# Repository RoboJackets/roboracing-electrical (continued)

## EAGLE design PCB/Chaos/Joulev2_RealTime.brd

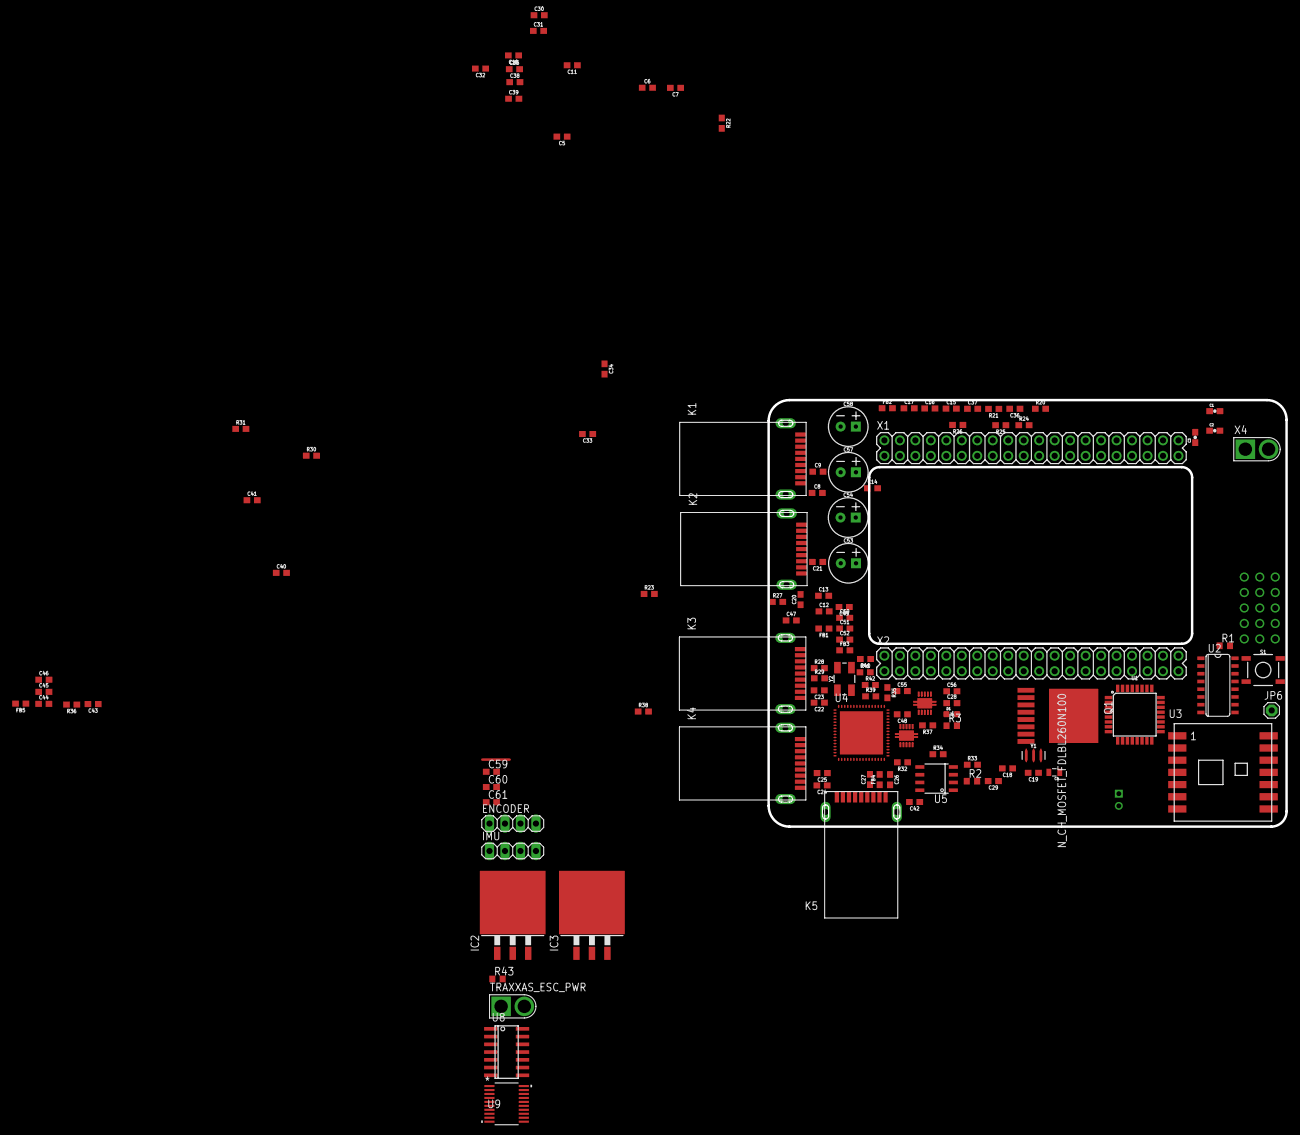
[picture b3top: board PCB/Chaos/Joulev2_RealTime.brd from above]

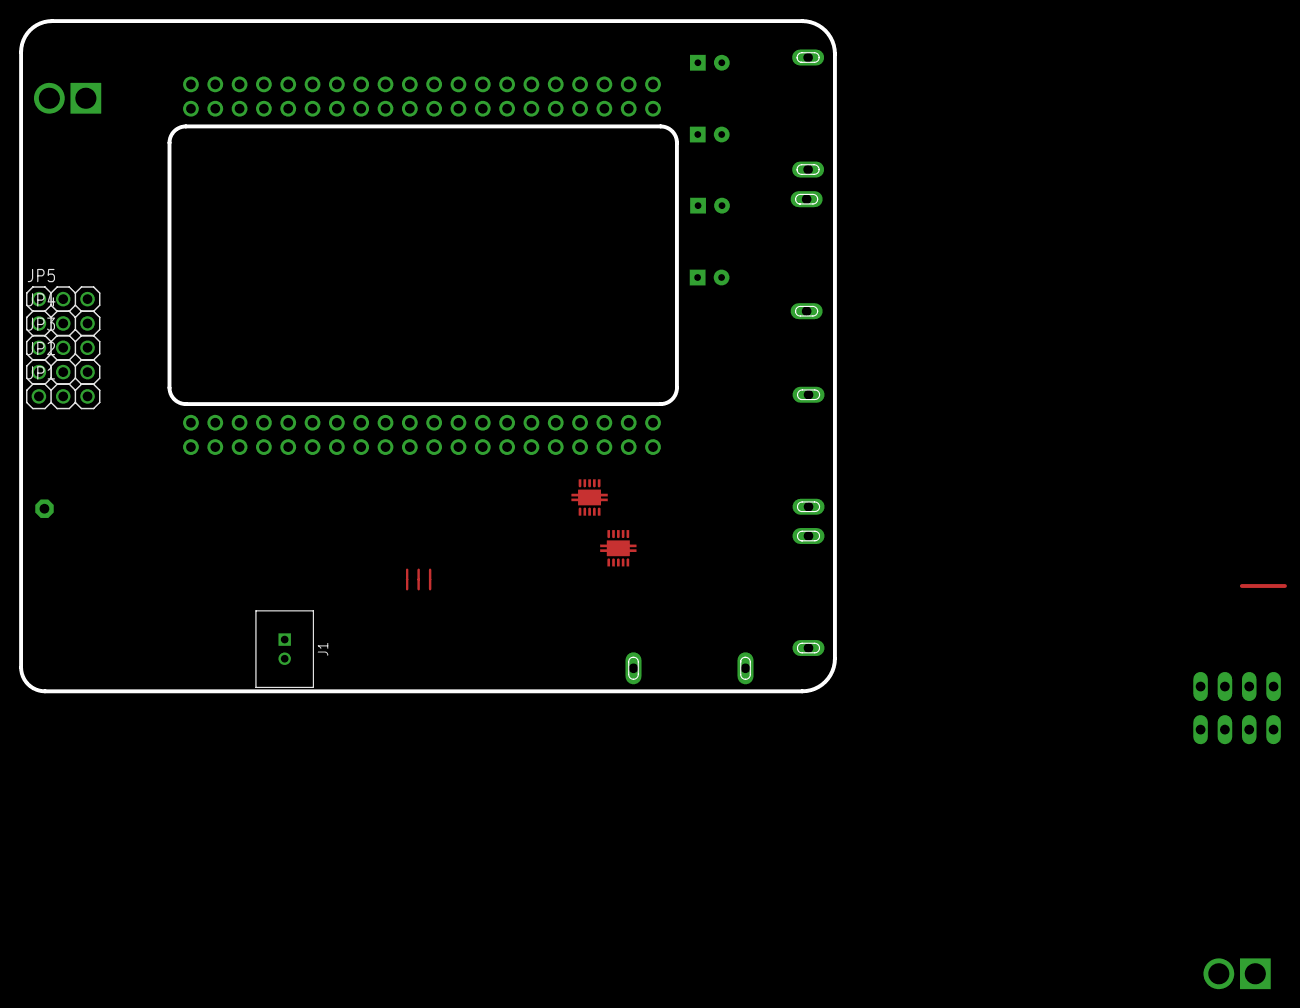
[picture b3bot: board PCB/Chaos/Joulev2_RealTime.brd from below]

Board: 2 copper layers, 85.0 x 70.0 mm, 127 parts (6 on the bottom side), 98 nets.

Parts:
C1: 0.22uF; 0603-CAP
C2: .1uF; 0603-CAP
C3: 0.1uF; 0603-CAP
C4: 10uf; 0805@1
C5, C10, C16, C19, C33: 1nF; 0603
C6, C8, C9, C12, C13, C17, C18, C20, C21, C22, C23, C24, C25, C26, C27, C28, C29, C31, C32, C35, C36, C37, C38, C39, C40, C41, C44, C45, C46, C47, C48, C49, C51, C52, C55, C56: 0.1uF; 0603
C7, C30, C50: 10uF; 0603
C11: 1.0uF; 0603
C14, C15: 18pF; 0603
C34, C43: 4.7uF; 0603
C42: 10nF; 0603
C53, C54, C57, C58: 150uF; CPOL-RADIAL-2.5MM-6.5MM
C59, C60: 0.1uF; C0603
C61: 10uF; C0603
D1: LED-0603
ENCODER: 1X04
FB1, FB2, FB3, FB5: 220@100MHz; 0603
FB4: 220@100Mhz; 0603
IC2, IC3: LM340S-12; TO263-3
IMU: 1X04
J1: 2-PIN_2MM-V; 2MM-2-V
JP1, JP2, JP3, JP4, JP5: 1X03
JP6: antenna; 1X01
K1, K2, K3, K4, K5: 692112030100
Q1: N_CH_MOSFET_FDLBL260N100; MO-299A
R1, R2, R43: 10k ohm; R0603
R3: 680 ohm; R0603
R20, R21, R26, R30, R31, R36: 1M; 0603
R22: 90.9k; 0603
R23, R39, R40, R41, R42: 10k; 0603
R24, R25, R27, R29, R32, R33, R34, R35: 4.7k; 0603
R28: 9.53k; 0603
R37, R38: 25.5k; 0603
S1: MOMENTARY-SWITCH 5.2mm; TACTILE_SWITCH_SMD_5.2MM
TRAXXAS_ESC_PWR: TRAXXAS-CON
U1: ATMEGA328P_TQFP; TQFP32-08
U2: 74VHC_MUXSO16; SO16
U3: RFM69CW; RFM69CW-XXXS2
U4: TUSB8041; QFN64-9X9
U5: ADP1706ARDZ-1.1-R7; SOIC8
U6, U7: TPS2561DRCT; 10-VSON
U8: SOIC-14
U9: TXB0108PWR; PW20
X1: J12HEADER_(JOULE); 2X20
X2: J13HEADER_(JOULE); 2X20
X4: TRAXXAS-CON
Y1: 16MHz; RESONATOR-SMD-3.2X1.3
Y2: 24MHz; CRYSTAL-SMD-5X3.2-4PAD

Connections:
1.1V: C30.1, C31.1, C32.1, C35.1, C38.1, C39.1, C40.1, C41.1, C43.1, U4.5, U4.8, U4.13, U4.21, U4.28, U4.31, U4.51, U4.57, U5.5, U5.6, U5.7
3.3V: C3.1, C4.1, C34.1, FB5.2, R32.2, R33.2, R34.2, R35.2, R39.2, R40.2, R41.2, R42.2, U3.2, U5.1, U5.3, U5.4
5V: C2.1, R1.1, R3.2, U1.4, U1.6, U1.18, U2.16
5V_MODE_SELECT: U1.12, U2.1
+3V3_HUB: C44.1, C45.1, C46.1, C47.1, C50.1, FB5.1
+5V: C48.1, C49.1, U6.2_1, U6.2_2, U6.3_1, U6.3_2, U7.2_1, U7.2_2, U7.3_1, U7.3_2
DN1_VBUS: C51.1, C53.1, FB1.1, U6.9_1, U6.9_2
DN2_VBUS: C55.1, C57.1, FB2.1, U6.8_1, U6.8_2
DN3_VBUS: C52.1, C54.1, FB3.1, U7.9_1, U7.9_2
ESTOP: J1.1, U1.2
ESTOP_GATE: J1.2, Q1.GATE, R2.1
GND: C1.2, C2.2, C3.2, C4.2, C5.1, C5.2, C6.1, C6.2, C7.2, C10.1, C10.2, C11.2, C12.2, C13.1, C13.2, C14.1, C15.1, C16.1, C16.2, C17.2, C18.1, C18.2, C19.1, C19.2, C28.2, C29.1, C29.2, C30.2, C31.2, C32.2, C33.1, C33.2, C34.2, C35.2, C36.2, C37.1, C37.2, C38.2, C39.2, C40.2, C41.2, C42.2, C43.2, C44.2, C45.2, C46.2, C47.2, C48.2, C49.2, C50.2, C51.2, C52.2, C53.2, C54.2, C55.2, C56.2, C57.2, C58.2, D1.C, JP1.1, JP2.1, JP3.1, JP4.1, K1.4, K1.7, K2.4, K2.7, K3.4, K3.7, K4.4, K5.4, Q1.P2, Q1.P3, Q1.P4, Q1.P5, Q1.P6, Q1.P7, Q1.P8, R2.2, R20.1, R20.2, R21.1, R21.2, R23.1, R24.1, R25.1, R27.1, R28.1, R29.1, R30.1, R30.2, R31.1, R31.2, R36.1, R36.2, R37.1, R38.1, S1.3, U1.3, U1.5, U1.21, U2.8, U3.3, U3.14, U4.16, U4.34, U4.52, U4.63, U4.EXP, U5.2, U6.1_1, U6.1_2, U6.PAD1, U6.PAD2, U6.PAD3, U7.1_1, U7.1_2, U7.PAD1, U7.PAD2, U7.PAD3, X1.36, X1.37, X1.38, X1.39, X2.1, X2.3, X2.5, X2.7, X2.9, X4.GND, Y1.2
GRST#: C11.1, U4.50
ILIM1: R37.2, U6.7_1, U6.7_2
ILIM2: R38.2, U7.7_1, U7.7_2
MISO_3P3V: U3.8, X2.29
MOSI_3P3V: U3.5, X2.27
unnamed: JP6.1, U3.1
unnamed: JP4.3, U2.4
unnamed: JP5.3, U2.7
unnamed: R1.2, S1.1, U1.29
unnamed: U1.7, Y1.1
unnamed: JP1.2, JP2.2, JP3.2, JP4.2, JP5.2
unnamed: U1.8, Y1.3
unnamed: R28.2, U4.64
unnamed: JP2.3, U2.3
unnamed: JP3.3, U2.6
unnamed: R29.2, U4.49
unnamed: D1.A, R3.1
unnamed: R27.2, U4.45
unnamed: R25.2, U4.42
unnamed: R24.2, U4.40
unnamed: R22.2, R23.2, U4.48
unnamed: C27.1, U4.27
unnamed: C26.1, U4.26
unnamed: C25.1, U4.20
unnamed: C24.1, U4.19
unnamed: C23.1, U4.12
unnamed: C22.1, U4.11
unnamed: C21.1, U4.4
unnamed: C20.1, U4.3
unnamed: C12.1, FB1.2, K2.1
unnamed: C42.1, U5.8
unnamed: C17.1, FB2.2
unnamed: C28.1, FB3.2, K4.1
unnamed: C56.1, C58.1, U7.8_1, U7.8_2
unnamed: C36.1, FB4.2, K5.1
OVERCUR1Z: R39.1, U4.46, U6.10_1, U6.10_2
OVERCUR2Z: R41.1, U4.47, U6.6_1, U6.6_2
OVERCUR3Z: R40.1, U4.44, U7.10_1, U7.10_2
OVERCUR4Z: R42.1, U4.43, U7.6_1, U7.6_2
PC_PWM_SERVO: U1.9, U2.2
PC_PWM_THROTTLE: U1.10, U2.5
PWRCTL1_BATEN1: R32.1, U4.36, U6.4_1, U6.4_2
PWRCTL2_BATEN2: R33.1, U4.35, U6.5_1, U6.5_2
PWRCTL3_BATEN3: R34.1, U4.33, U7.4_1, U7.4_2
PWRCTL4_BATEN4: R35.1, U4.32, U7.5_1, U7.5_2
RC_MODE: JP1.3, U1.11
S$2: X2.6, X2.8
SCK_3P3V: U3.6, X2.25
USBA_USB2_1_DN: K1.2, U4.54
USBA_USB2_1_DP: K1.3, U4.53
USBA_USB3_1_RX_DN: K1.5, U4.59
USBA_USB3_1_RX_DP: K1.6, U4.58
USBA_USB3_1_TX_DN: C9.1, K1.8
USBA_USB3_1_TX_DP: C8.1, K1.9
USB_DM_DN1: K2.2, U4.2
USB_DM_DN2: K3.2, U4.10
USB_DM_DN3: K4.2, U4.18
USB_DM_DN4: K5.2, U4.25
USB_DP_DN1: K2.3, U4.1
USB_DP_DN2: K3.3, U4.9
USB_DP_DN3: K4.3, U4.17
USB_DP_DN4: K5.3, U4.24
USB_SSRXM_DN1: K2.5, U4.7
USB_SSRXM_DN2: K3.5, U4.15
USB_SSRXM_DN3: K4.5, U4.23
USB_SSRXM_DN4: K5.5, U4.30
USB_SSRXP_DN1: K2.6, U4.6
USB_SSRXP_DN2: K3.6, U4.14
USB_SSRXP_DN3: K4.6, U4.22
USB_SSRXP_DN4: K5.6, U4.29
USB_SSTXM_DN1: C21.2, K2.8
USB_SSTXM_DN2: C23.2, K3.8
USB_SSTXM_DN3: C25.2, K4.8
USB_SSTXM_DN4: C27.2, K5.8
USB_SSTXP_DN1: C20.2, K2.9
USB_SSTXP_DN2: C22.2, K3.9
USB_SSTXP_DN3: C24.2, K4.9
USB_SSTXP_DN4: C26.2, K5.9
V1P8V: X2.10, X2.12
V5P0V: X2.2, X2.4
VBUS_HUB: C7.1, K1.1, R22.1
VCC: C1.1, X4.V+
X: C8.2, U4.55
XI: C15.2, R26.2, U4.62, Y2.3
XO: C14.2, R26.1, U4.61, Y2.1
Y: C9.2, U4.56

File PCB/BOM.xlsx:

Qty | Value | Device | Package | Parts | Description | MANUFACTURER_PART_NUMBER | PINS | PIN_PITCH | PROD_ID | SF_ID | SF_SKU | VALUE | VENDOR
1 |  | LED0603 | LED-0603 | D1 | LEDs
5 |  | PINHD-1X3 | 1X03 | JP1, JP2, JP3, JP4, JP5 | PIN HEADER
2 |  | PINHD-1X4 | 1X04 | ENCODER, IMU | PIN HEADER
1 | .1uF | 0.22UF-25V-10%(0603) | 0603-CAP | C2 | CAP-07822 |  |  |  | CAP-07822 |  |  | 0.22uF
36 | 0.1uF | 0.1UF-0603-25V-(+80/-20%) | 603 | C6, C8, C9, C12, C13, C17, C18, C20, C21, C22, C23, C24, C25, C26, C27, C28, C2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 | 0.1ｵF ceramic capacitors |  |  |  | CAP-00810 |  |  | 0.1uF
1 | 0.1uF | 0.1UF-25V(+80/-20%)(0603) | 0603-CAP | C3 | CAP-00810 |  |  |  | CAP-00810 |  |  | 0.1uF
2 | 0.1uF | C-USC0603 | C0603 | C59, C60 | CAPACITOR, American symbol
1 | 0.22uF | 0.22UF-25V-10%(0603) | 0603-CAP | C1 | CAP-07822 |  |  |  | CAP-07822 |  |  | 0.22uF
1 | 1.0uF | 1.0UF-0603-16V-10% | 603 | C11 | 1ｵF ceramic capacitors |  |  |  | CAP-00868 |  |  | 1.0uF
5 | 10k | 10KOHM-0603-1/10W-1% | 603 | R23, R39, R40, R41, R42 | 10kO resistor |  |  |  | RES-00824 |  |  | 10k
3 | 10k ohm | R-US_R0603 | R0603 | R1, R2, R43 | RESISTOR, American symbol
1 | 10nF | 10NF-0603-50V-10% | 603 | C42 | 0.01uF/10nF/10,000pF ceramic capacitors |  |  |  | CAP-00867 |  |  | 10nF
3 | 10uF | 10UF-0603-6.3V-20% | 603 | C7, C30, C50 | 10.0ｵF ceramic capacitors |  |  |  | CAP-11015 |  |  | 10uF
1 | 10uF | C-USC0603 | C0603 | C61 | CAPACITOR, American symbol
1 | 10uf | 2.2UF-25V-+80/-20(0805) | 0805@1 | C4 | CAP-11624 |  |  |  | CAP-11624 |  |  | 2.2uF
4 | 150uF | 100UF-POLAR-RADIAL-2.5MM-25V-20% | CPOL-RADIAL-2.5MM-6.5MM | C53, C54, C57, C58 | 100ｵF polarized capacitors |  |  |  | CAP-08439 |  |  | 100uF
1 | 16MHz | RESONATOR-16MHZSMD_3.2X1.3 | RESONATOR-SMD-3.2X1.3 | Y1 | 16MHz Resonator |  |  |  | XTAL-08900 |  |  | 16MHz
2 | 18pF | 18PF-0603-50V-5% | 603 | C14, C15 | 18pF ceramic capacitors |  |  |  | CAP-08267 |  |  | 18pF
6 | 1M | 1MOHM-0603-1/4W-5% | 603 | R20, R21, R26, R30, R31, R36 | 1MO resistor |  |  |  | RES-07868 |  |  | 1M
5 | 1nF | 1.0NF/1000PF-0603-50V-10% | 603 | C5, C10, C16, C19, C33 | 1nF/1,000pF ceramic capacitors |  |  |  | CAP-07886 |  |  | 1nF
1 | 2-PIN_2MM-V | 2-PIN_2MM-V | 2MM-2-V | J1 |  |  | 2 | 2.0 mm
4 | 220@100MHz | FERRITE_BEAD-0603 | 603 | FB1, FB2, FB3, FB5 | Ferrite Bead (blocks, cores, rings, chokes, etc.) |  |  |  | NDUC-07859 |  |  | 30O/1.8A
1 | 220@100Mhz | FERRITE_BEAD-0603 | 603 | FB4 | Ferrite Bead (blocks, cores, rings, chokes, etc.) |  |  |  | NDUC-07859 |  |  | 30O/1.8A
1 | 24MHz | CRYSTAL-24MHZ";CRYSTAL-SMD-5X3.2-4PAD" | Y2 | 24MHz Crystal |  |  |  | XTAL-08298 | COM-08581 |  | 24MHz
2 | 25.5k | 26.7KOHM0603-1/10W-1% | 603 | R37, R38 | 26.7kO resistor |  |  |  | RES-12186 |  |  | 26.7k
8 | 4.7k | 4.7KOHM-0603-1/10W-1% | 603 | R24, R25, R27, R29, R32, R33, R34, R35 | 4.7kO resistor |  |  |  | RES-07857 |  |  | 4.7k
2 | 4.7uF | 4.7UF0603 | 603 | C34, C43 | 4.7ｵF ceramic capacitors |  |  |  | CAP-08280 |  |  | 4.7uF
1 | 680 ohm | R-US_R0603 | R0603 | R3 | RESISTOR, American symbol
5 | 692112030100 | 692112030100 | 692112030100 | K1, K2, K3, K4, K5 | WR-COM USB 3.0 SMT PLUG WITH CLIPTYPE A
1 | 74VHC_MUXSO16 | 74VHC_MUXSO16 | SO16 | U2
1 | 9.53k | 9.76KOHM-0603-1/10W-1% | 603 | R28 | 9.76kO resistor |  |  |  | RES-12534 |  |  | 9.76k
1 | 90.9k | 100KOHM-0603-1/10W-1% | 603 | R22 | 100kO resistor |  |  |  | RES-07828 |  |  | 100k
1 | ADP1706ARDZ-1.1-R7 | ADP1706ARDZ-1.1-R7 | SOIC8 | U5
1 | ATMEGA328P_TQFP | ATMEGA328P_TQFP | TQFP32-08 | U1 | Popular 328P in QFP |  |  |  | IC-09069 |  |  | ATMEGA328P_TQFP
1 | ATTINY441/841SSU/SSUR | ATTINY441/841SSU/SSUR | SOIC-14 | U8
1 | J12HEADER_(JOULE) | J12HEADER_(JOULE) | 2X20 | X1
1 | J13HEADER_(JOULE) | J13HEADER_(JOULE) | 2X20 | X2
2 | LM340S-12 | LM340S-12 | TO263-3 | IC2, IC3 | Positive VOLTAGE REGULATOR
1 | MOMENTARY-SWITCH 5.2mm | MOMENTARY-SWITCH-SPST-SMD-5.2MM | TACTILE_SWITCH_SMD_5.2MM | S1 | Momentary Switch (Pushbutton) - SPST |  |  |  | SWCH-08247 |  | COM-08720
1 | N_CH_MOSFET_FDLBL260N100 | N_CH_MOSFET_FDLBL260N100 | MO-299A | Q1
1 | RFM69CW | RFM69CW | RFM69CW-XXXS2 | U3
2 | TPS2561DRCT | TPS2561DRCT | 10-VSON | U6, U7
2 | TRAXXAS-CON | TRAXXAS-CON | TRAXXAS-CON | TRAXXAS_ESC_PWR, X4
1 | TUSB8041 | TUSB8041 | QFN64-9X9 | U4
1 | TXB0108PWR | TXB0108PWR | PW20 | U9 |  | TXB0108PWR |  |  |  |  |  |  | Texas Instruments
1 | antenna | PINHD-1X1 | 1X01 | JP6 | Pin header 1x1 for 0.1 spacing"

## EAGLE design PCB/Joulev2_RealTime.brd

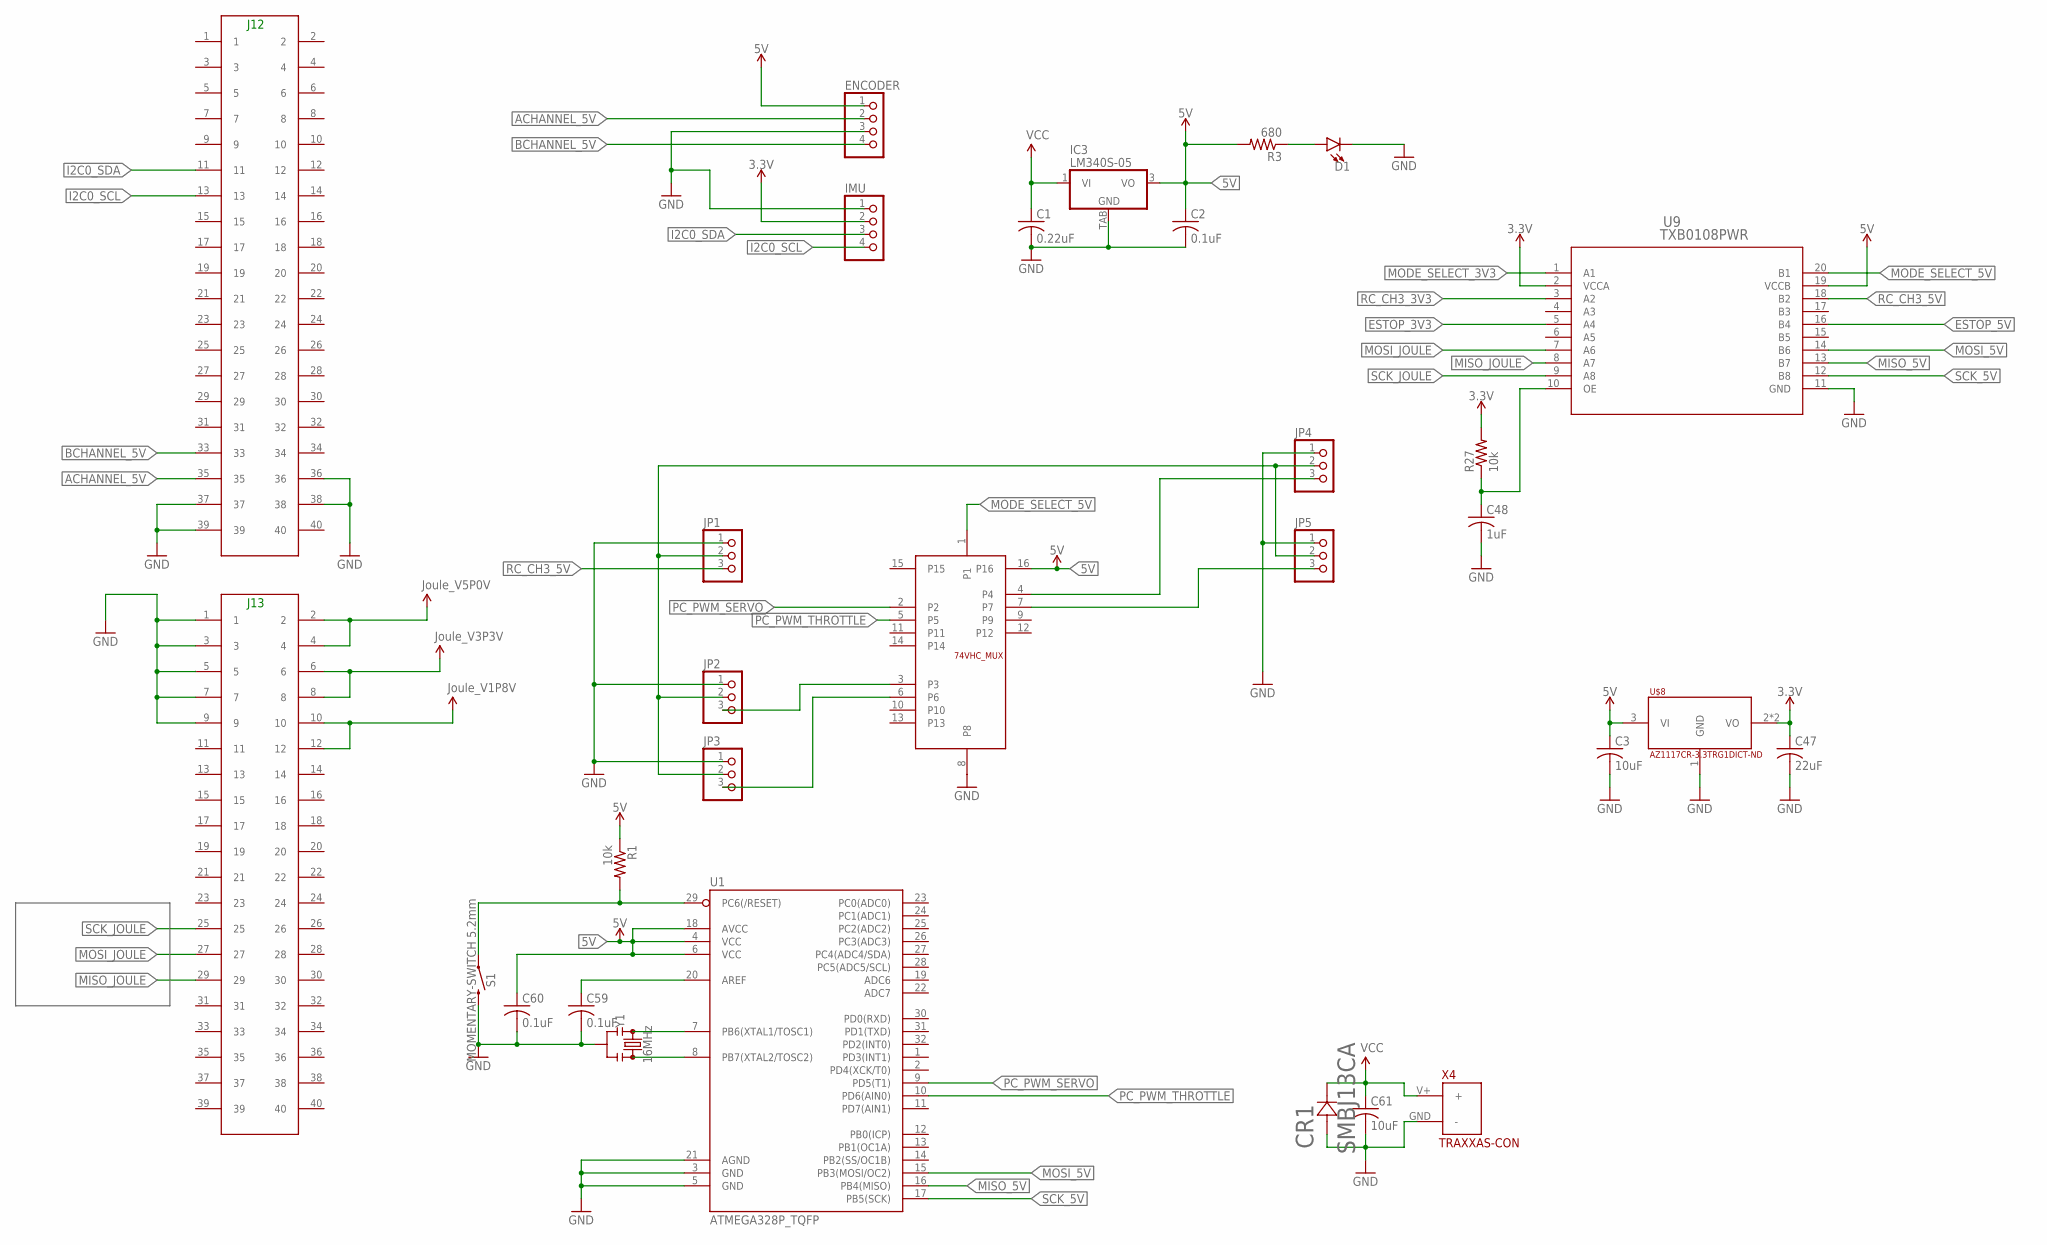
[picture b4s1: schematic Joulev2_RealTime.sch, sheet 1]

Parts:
C1: 0.22uF; C0603
C2, C59, C60: 0.1uF; C0603
C3, C61: 10uF; C0603
C47: 22uF; C0603
C48: 1uF; C0603
CR1: SMBJ13CA; SMB
D1: LED0603; LED-0603
ENCODER: PINHD-1X4; 1X04
IC3: LM340S-05; TO263-3
IMU: PINHD-1X4; 1X04
JP1, JP2, JP3, JP4, JP5: PINHD-1X3; 1X03
R1, R27: 10k; R0603
R3: 680; R0603
S1: MOMENTARY-SWITCH 5.2mm; TACTILE_SWITCH_SMD_5.2MM
U1: ATMEGA328P_TQFP; TQFP32-08
U2: 74VHC_MUXSO16; SO16
U9: TXB0108PWR; PW20
U$8: AZ1117CR-3.3TRG1DICT-ND; SOT89R_INFINEON
X1: J12HEADER_(JOULE); 2X20
X2: J13HEADER_(JOULE); 2X20
X4: TRAXXAS-CON
Y1: 16MHz; RESONATOR-SMD-3.2X1.3

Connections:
3.3V: C47.1, IMU.2, R27.2, U9.2 (VCCA), U$8.2 (VO), U$8.4 (VO); also elsewhere on the board
5V: C2.1, C3.1, C60.1, ENCODER.1, IC3.3 (VO), JP1.2, JP2.2, JP3.2, JP4.2, JP5.2, R1.1, R3.2, U1.4 (VCC), U1.6 (VCC), U1.18 (AVCC), U2.16, U9.19 (VCCB), U$8.3 (VI); also elsewhere on the board
ACHANNEL_5V: ENCODER.2, X1.35
BCHANNEL_5V: ENCODER.4, X1.33
ESTOP_3V3: U9.5 (A4); also elsewhere on the board
ESTOP_5V: U9.16 (B4); also elsewhere on the board
GND: C1.2, C2.2, C3.2, C47.2, C48.2, C59.2, C60.2, C61.2, CR1.2 (22), D1.C, ENCODER.3, IC3.TAB (GND), IMU.1, JP1.1, JP2.1, JP3.1, JP4.1, JP5.1, S1.3 (2), U1.3 (GND), U1.5 (GND), U1.21 (AGND), U2.8, U9.11 (GND), U$8.1 (GND), X1.36, X1.37, X1.38, X1.39, X2.1, X2.3, X2.5, X2.7, X2.9, X4.GND (-), Y1.2; also elsewhere on the board
I2C0_SCL: IMU.4, X1.13
I2C0_SDA: IMU.3, X1.11
MISO_5V: U1.16 (PB4(MISO)), U9.13 (B7)
MISO_JOULE: U9.8 (A7), X2.29
MODE_SELECT_3V3: U9.1 (A1); also elsewhere on the board
MODE_SELECT_5V: U2.1, U9.20 (B1)
MOSI_5V: U1.15 (PB3(MOSI/OC2)), U9.14 (B6)
MOSI_JOULE: U9.7 (A6), X2.27
unnamed: JP4.3, U2.4
unnamed: JP5.3, U2.7
unnamed: R1.2, S1.1, U1.29 (PC6(/RESET))
unnamed: U1.7 (PB6(XTAL1/TOSC1)), Y1.1
unnamed: U1.8 (PB7(XTAL2/TOSC2)), Y1.3
unnamed: JP2.3, U2.3
unnamed: JP3.3, U2.6
unnamed: C59.1, U1.20 (AREF)
unnamed: D1.A, R3.1
unnamed: C48.1, R27.1, U9.10 (OE)
PC_PWM_SERVO: U1.9 (PD5(T1)), U2.2
PC_PWM_THROTTLE: U1.10 (PD6(AIN0)), U2.5
RC_CH3_3V3: U9.3 (A2); also elsewhere on the board
RC_CH3_5V: JP1.3, U9.18 (B2)
SCK_5V: U1.17 (PB5(SCK)), U9.12 (B8)
SCK_JOULE: U9.9 (A8), X2.25
V1P8V: X2.10, X2.12
V3P3V: X2.6, X2.8
V5P0V: X2.2, X2.4
VCC: C1.1, C61.1, CR1.1 (11), IC3.1 (VI), X4.V+ (+); also elsewhere on the board

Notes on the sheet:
J12
J13

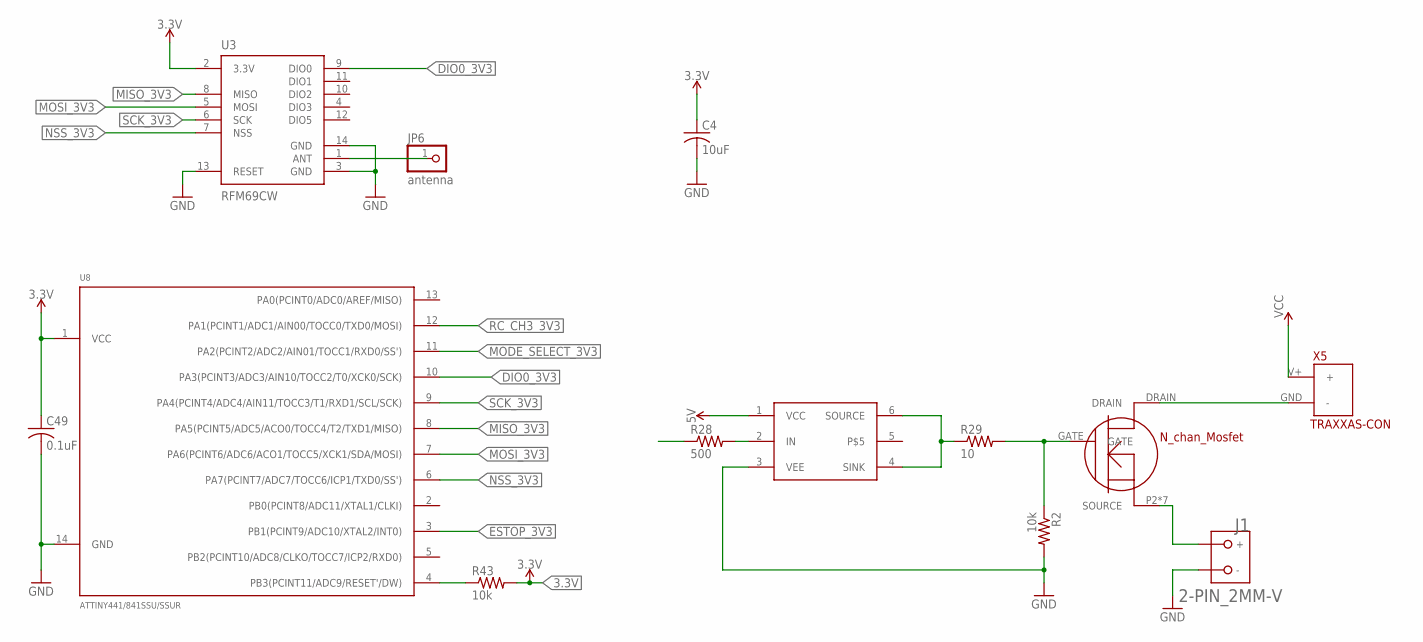
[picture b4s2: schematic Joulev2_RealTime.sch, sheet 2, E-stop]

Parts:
C4: 10uF; C0603
C49: 0.1uF; C0603
J1: 2-PIN_2MM-V; 2MM-2-V
JP6: antenna; 1X01
Q1: N_CH_MOSFET_FDLBL260N100; MO-299A
R2, R43: 10k; R0603
R28: 500; R0603
R29: 10; R0603
U3: RFM69CW; RFM69CW-XXXS2
U8: ATTINY441/841SSU/SSUR; SOIC-14
U10: ZXGD3009DY; SOT363
X5: TRAXXAS-CON

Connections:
3.3V: C4.1, C49.1, R43.2, U3.2 (3.3V), U8.1 (VCC); also elsewhere on the board
5V: U10.1 (VCC); also elsewhere on the board
DIO0_3V3: U3.9 (DIO0), U8.10 (PA3(PCINT3/ADC3/AIN10/TOCC2/T0/XCK0/SCK))
ESTOP_3V3: U8.3 (PB1(PCINT9/ADC10/XTAL2/INT0)); also elsewhere on the board
ESTOP_5V: R28.1; also elsewhere on the board
GND: C4.2, C49.2, J1.2 (-), R2.2, U3.3 (GND), U3.13 (RESET), U3.14 (GND), U8.14 (GND), U10.3 (VEE); also elsewhere on the board
MISO_3V3: U3.8 (MISO), U8.8 (PA5(PCINT5/ADC5/ACO0/TOCC4/T2/TXD1/MISO))
MODE_SELECT_3V3: U8.11 (PA2(PCINT2/ADC2/AIN01/TOCC1/RXD0/SS')); also elsewhere on the board
MOSI_3V3: U3.5 (MOSI), U8.7 (PA6(PCINT6/ADC6/ACO1/TOCC5/XCK1/SDA/MOS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)
unnamed: JP6.1, U3.1 (ANT)
unnamed: Q1.DRAIN, X5.GND (-)
unnamed: R28.2, U10.2 (IN)
unnamed: R43.1, U8.4 (PB3(PCINT11/ADC9/RESET'/DW))
unnamed: R29.1, U10.4 (SINK), U10.6 (SOURCE)
unnamed: J1.1 (+), Q1.P2 (SOURCE), Q1.P3 (SOURCE), Q1.P4 (SOURCE), Q1.P5 (SOURCE), Q1.P6 (SOURCE), Q1.P7 (SOURCE), Q1.P8 (SOURCE)
unnamed: Q1.GATE, R2.1, R29.2
NSS_3V3: U3.7 (NSS), U8.6 (PA7(PCINT7/ADC7/TOCC6/ICP1/TXD0/SS'))
RC_CH3_3V3: U8.12 (PA1(PCINT1/ADC1/AIN00/TOCC0/TXD0/MOSI)); also elsewhere on the board
SCK_3V3: U3.6 (SCK), U8.9 (PA4(PCINT4/ADC4/AIN11/TOCC3/T1/RXD1/SCL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)
VCC: X5.V+ (+); also elsewhere on the board

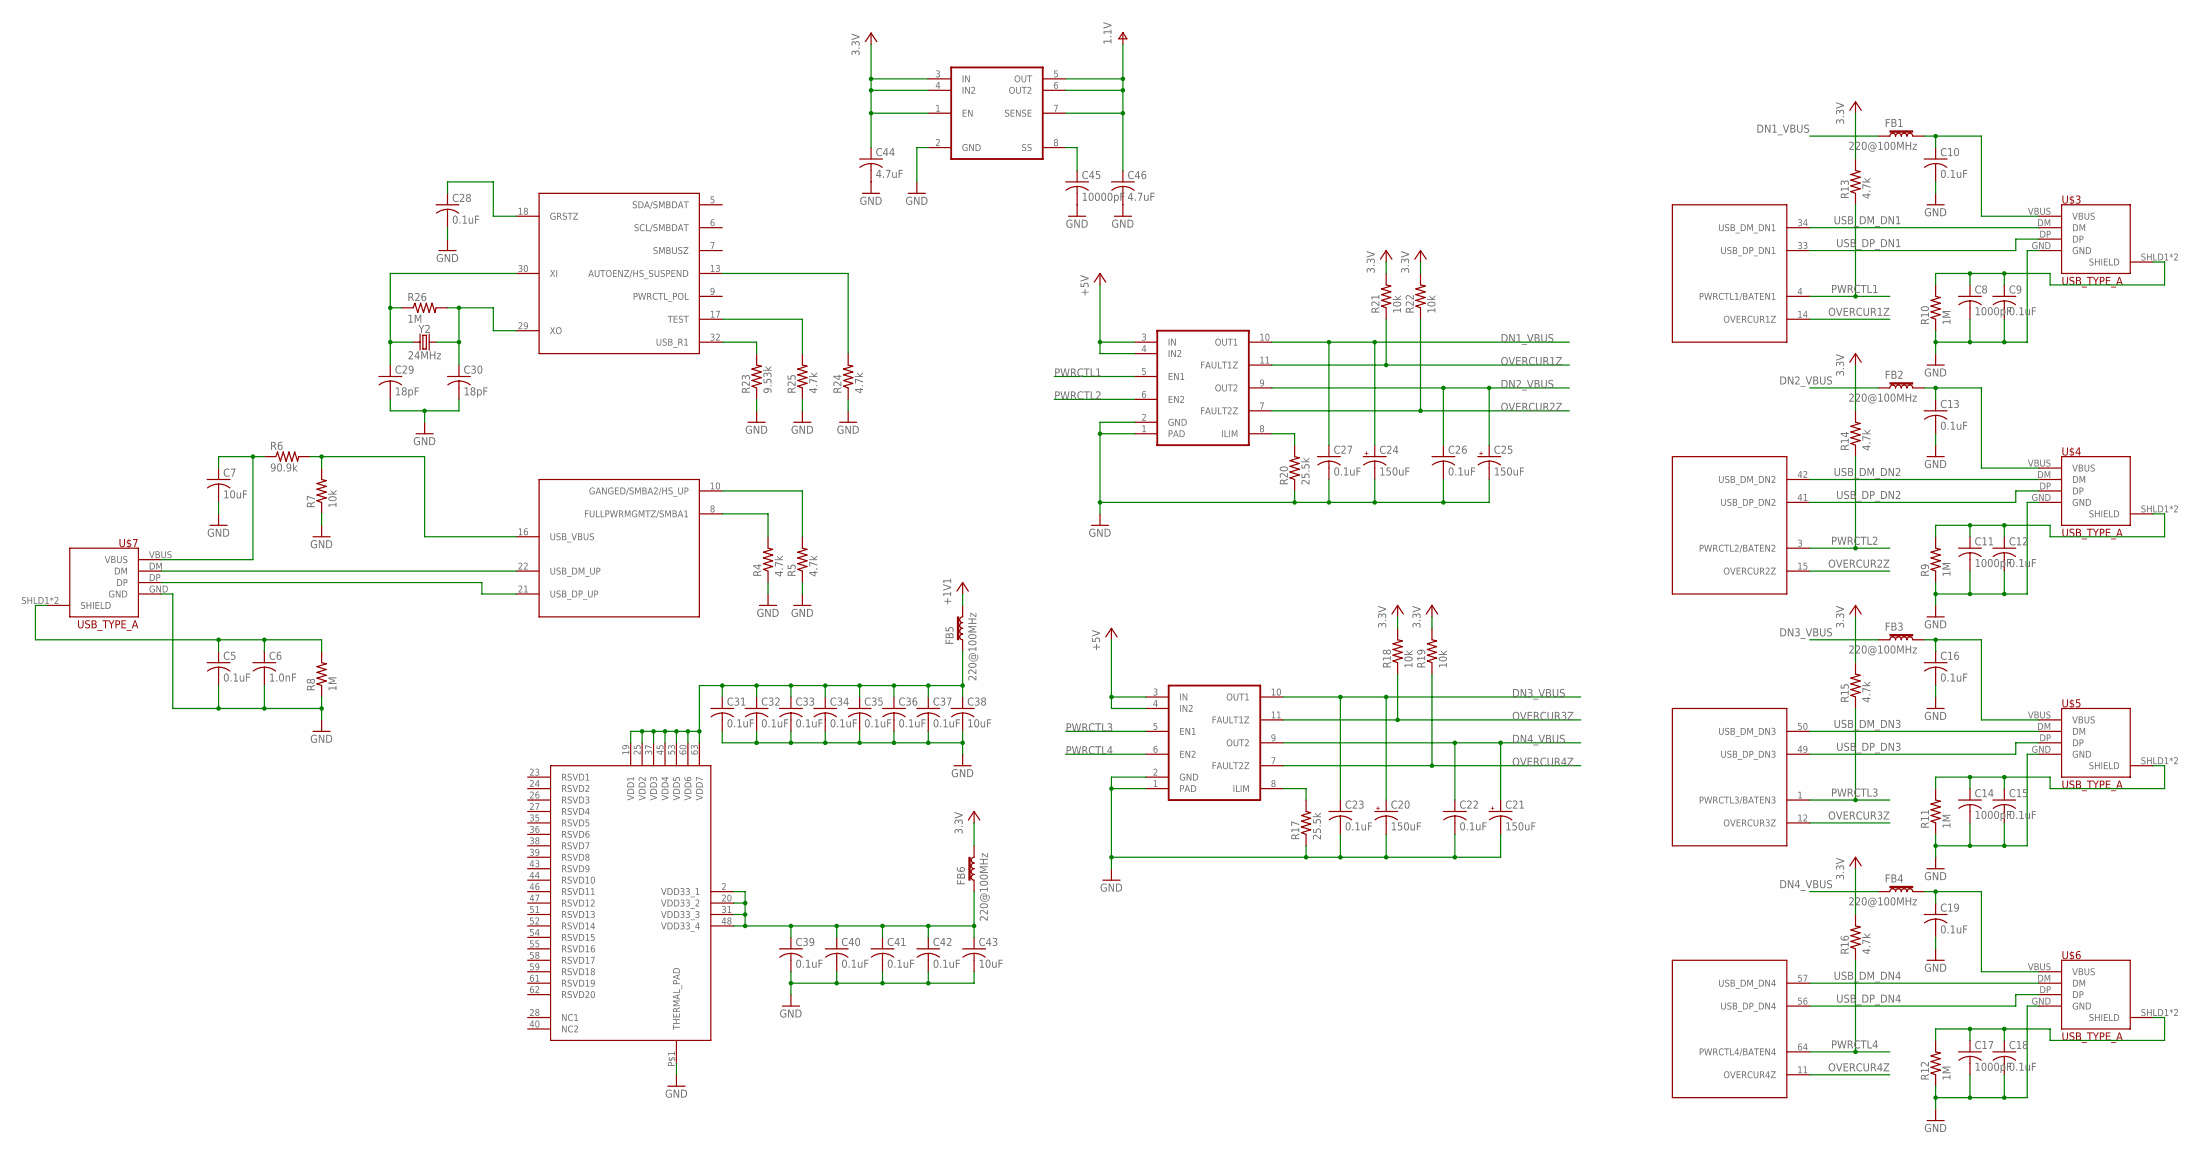
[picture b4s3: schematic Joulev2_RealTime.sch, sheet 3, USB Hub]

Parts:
C5, C9, C10, C12, C13, C15, C16, C18, C19, C22, C23, C26, C27, C28, C31, C32, C33, C34, C35, C36, C37, C39, C40, C41, C42: 0.1uF; C0603
C6: 1.0nF; C0603
C7, C38, C43: 10uF; C0603
C8, C11, C14, C17: 1000pF; C0603
C20, C21, C24, C25: 150uF; E3,5-8
C29, C30: 18pF; C0603
C44, C46: 4.7uF; C0603
C45: 10000pF; C0603
FB1, FB2, FB3, FB4, FB5, FB6: 220@100MHz; 0603
R4, R5, R13, R14, R15, R16, R24, R25: 4.7k; R0603
R6: 90.9k; R0603
R7, R18, R19, R21, R22: 10k; R0603
R8, R9, R10, R11, R12, R26: 1M; R0603
R17, R20: 25.5k; R0603
R23: 9.53k; R0603
U4: ADP1706ARDZ-1.1-R7; SOIC8
U$1: TUSB4041; TQFP64-10X10
U$3, U$4, U$5, U$6, U$7: USB_TYPE_A
U$10, U$11: TPS2561DRCT; 10-VSON
Y2: 24MHz; CRYSTAL-SMD-5X3.2-4PAD

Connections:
1.1V: C46.1, FB5.2, U4.5 (OUT), U4.6 (OUT2), U4.7 (SENSE)
3.3V: C44.1, FB6.2, R13.2, R14.2, R15.2, R16.2, R18.2, R19.2, R21.2, R22.2, U4.1 (EN), U4.3 (IN), U4.4 (IN2); also elsewhere on the board
5V: U$10.3 (IN), U$10.4 (IN2), U$11.3 (IN), U$11.4 (IN2); also elsewhere on the board
DN1_VBUS: C24.+, C27.1, FB1.1, U$11.10 (OUT1)
DN2_VBUS: C25.+, C26.1, FB2.1, U$11.9 (OUT2)
DN3_VBUS: C20.+, C23.1, FB3.1, U$10.10 (OUT1)
DN4_VBUS: C21.+, C22.1, FB4.1, U$10.9 (OUT2)
GND: C5.2, C6.2, C7.2, C8.2, C9.2, C10.2, C11.2, C12.2, C13.2, C14.2, C15.2, C16.2, C17.2, C18.2, C19.2, C20.-, C21.-, C22.2, C23.2, C24.-, C25.-, C26.2, C27.2, C28.2, C29.2, C30.2, C31.2, C32.2, C33.2, C34.2, C35.2, C36.2, C37.2, C38.2, C39.2, C40.2, C41.2, C42.2, C43.2, C44.2, C45.2, C46.2, R4.1, R5.1, R7.1, R8.1, R9.1, R10.1, R11.1, R12.1, R17.1, R20.1, R23.1, R24.1, R25.1, U4.2 (GND), U$1.P$1 (THERMAL_PAD), U$3.GND, U$4.GND, U$5.GND, U$6.GND, U$7.GND, U$10.1 (PAD), U$10.2 (GND), U$11.1 (PAD), U$11.2 (GND); also elsewhere on the board
unnamed: R4.2, U$1.8 (FULLPWRMGMTZ/SMBA1)
unnamed: R5.2, U$1.10 (GANGED/SMBA2/HS_UP)
unnamed: R6.2, R7.2, U$1.16 (USB_VBUS)
unnamed: C7.1, R6.1, U$7.VBUS
unnamed: C13.1, FB2.2, U$4.VBUS
unnamed: C5.1, C6.1, R8.2, U$7.SHLD1 (SHIELD), U$7.SHLD2 (SHIELD)
unnamed: U$1.22 (USB_DM_UP), U$7.DM
unnamed: U$1.21 (USB_DP_UP), U$7.DP
unnamed: C16.1, FB3.2, U$5.VBUS
unnamed: C10.1, FB1.2, U$3.VBUS
unnamed: C19.1, FB4.2, U$6.VBUS
unnamed: R20.2, U$11.8 (ILIM)
unnamed: C28.1, U$1.18 (GRSTZ)
unnamed: R23.2, U$1.32 (USB_R1)
unnamed: R17.2, U$10.8 (ILIM)
unnamed: C29.1, R26.1, U$1.30 (XI), Y2.1
unnamed: C30.1, R26.2, U$1.29 (XO), Y2.3 (2)
unnamed: R25.2, U$1.17 (TEST)
unnamed: C39.1, C40.1, C41.1, C42.1, C43.1, FB6.1, U$1.2 (VDD33_1), U$1.20 (VDD33_2), U$1.31 (VDD33_3), U$1.48 (VDD33_4)
unnamed: R24.2, U$1.13 (AUTOENZ/HS_SUSPEND)
unnamed: C31.1, C32.1, C33.1, C34.1, C35.1, C36.1, C37.1, C38.1, FB5.1, U$1.19 (VDD1), U$1.25 (VDD2), U$1.37 (VDD3), U$1.45 (VDD4), U$1.53 (VDD5), U$1.60 (VDD6), U$1.63 (VDD7)
unnamed: C17.1, C18.1, R12.2, U$6.SHLD1 (SHIELD), U$6.SHLD2 (SHIELD)
unnamed: C14.1, C15.1, R11.2, U$5.SHLD1 (SHIELD), U$5.SHLD2 (SHIELD)
unnamed: C8.1, C9.1, R10.2, U$3.SHLD1 (SHIELD), U$3.SHLD2 (SHIELD)
unnamed: C11.1, C12.1, R9.2, U$4.SHLD1 (SHIELD), U$4.SHLD2 (SHIELD)
unnamed: C45.1, U4.8 (SS)
OVERCUR1Z: R21.1, U$1.14 (OVERCUR1Z), U$11.11 (FAULT1Z)
OVERCUR2Z: R22.1, U$1.15 (OVERCUR2Z), U$11.7 (FAULT2Z)
OVERCUR3Z: R18.1, U$1.12 (OVERCUR3Z), U$10.11 (FAULT1Z)
OVERCUR4Z: R19.1, U$1.11 (OVERCUR4Z), U$10.7 (FAULT2Z)
PWRCTL1: R13.1, U$1.4 (PWRCTL1/BATEN1), U$11.5 (EN1)
PWRCTL2: R14.1, U$1.3 (PWRCTL2/BATEN2), U$11.6 (EN2)
PWRCTL3: R15.1, U$1.1 (PWRCTL3/BATEN3), U$10.5 (EN1)
PWRCTL4: R16.1, U$1.64 (PWRCTL4/BATEN4), U$10.6 (EN2)
USB_DM_DN1: U$1.34 (USB_DM_DN1), U$3.DM
USB_DM_DN2: U$1.42 (USB_DM_DN2), U$4.DM
USB_DM_DN3: U$1.50 (USB_DM_DN3), U$5.DM
USB_DM_DN4: U$1.57 (USB_DM_DN4), U$6.DM
USB_DP_DN1: U$1.33 (USB_DP_DN1), U$3.DP
USB_DP_DN2: U$1.41 (USB_DP_DN2), U$4.DP
USB_DP_DN3: U$1.49 (USB_DP_DN3), U$5.DP
USB_DP_DN4: U$1.56 (USB_DP_DN4), U$6.DP
